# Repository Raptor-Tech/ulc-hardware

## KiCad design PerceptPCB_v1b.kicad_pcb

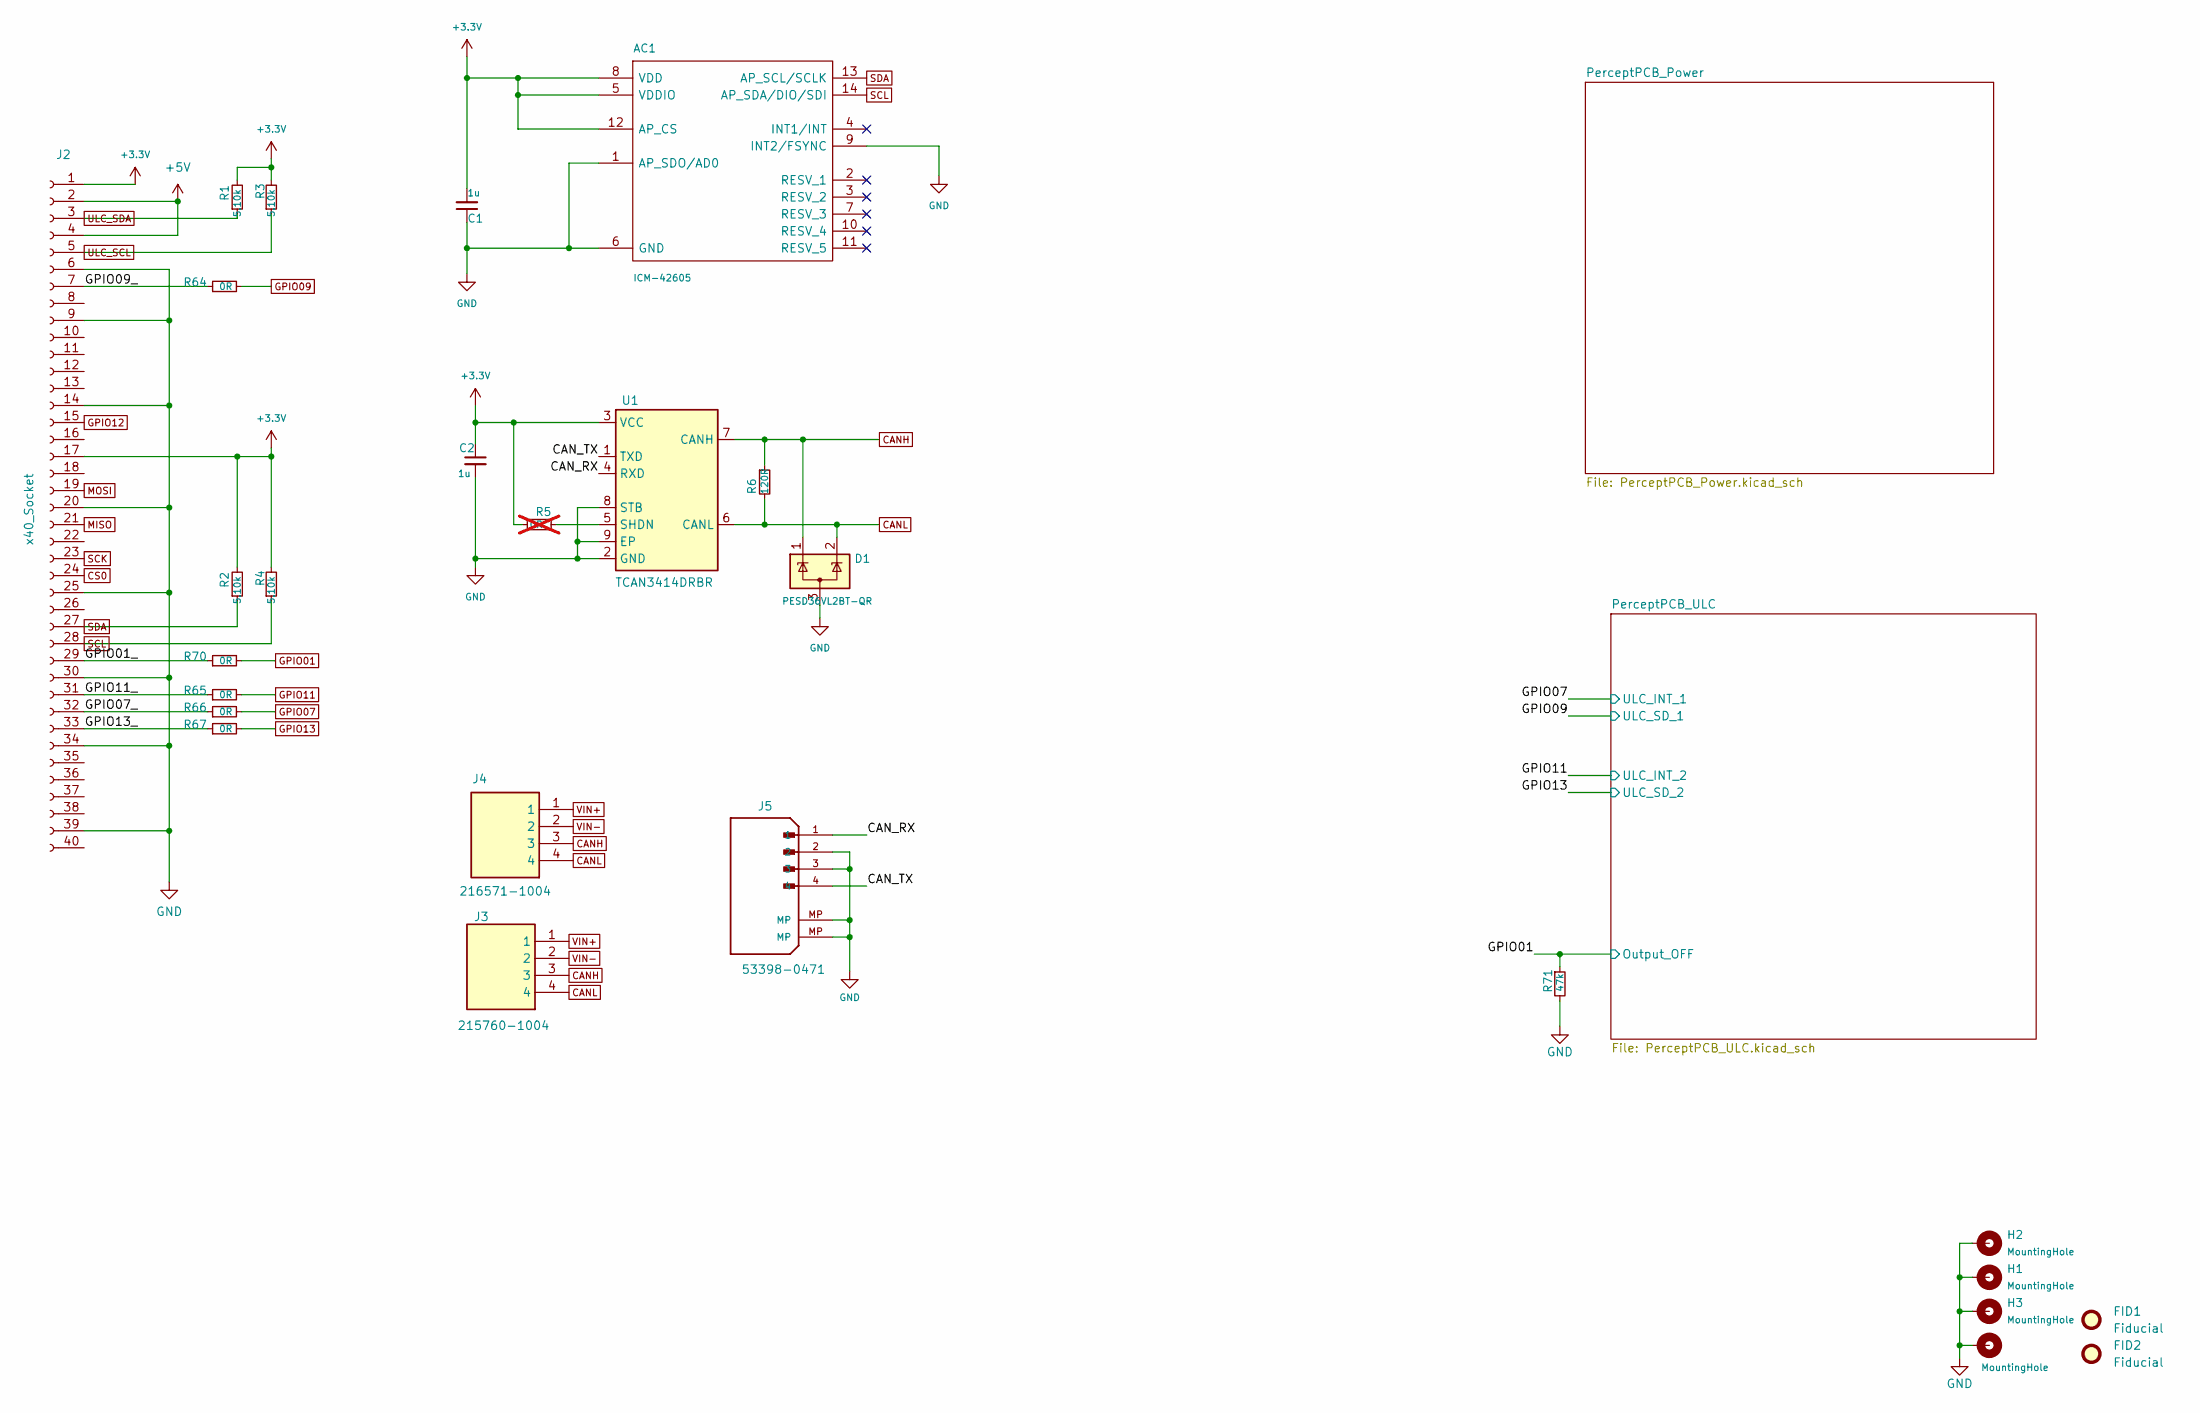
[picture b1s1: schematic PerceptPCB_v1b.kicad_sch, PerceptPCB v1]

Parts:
AC1: ICM-42605; IIM42352; MPN ICM-42605
C1, C2: 1u; C_0603_1608Metric; MPN C1608X7R2A105K080AC
D1: PESD36VL2BT-QR; SOT-23; MPN PESD36VL2BT-QR
FID1, FID2: Fiducial; Fiducial_1mm_Mask2mm
H1, H2, H3: MountingHole; MountingHole_2.7mm_M2.5_ISO14580_Pad
H4: MountingHole; Mounting_Wuerth_WA-SMSI-M1.6_H2.5mm_ThreadDepth1.5mm_NoNPTH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
J2: x40_Socket; PinSocket_2x20_P2.54mm_Vertical_SMD; MPN HLE-120-02-L-DV-BE-A-P-TR
J3: 215760-1004; 215760-YY04; Mouser Part Number 538-215760-1004
J4: 216571-1004; 216571-YY04_1; Mouser Part Number 538-216571-1004
J5: 53398-0471; Molex_PicoBlade_53398-0471_1x04-1MP_P1.25mm_Vertical; MPN 53398-0471
R1, R2, R3, R4: 5.10k; R_0603_1608Metric; MPN RMCF0603FT5K10
R5: 0R; R_0603_1608Metric; MPN RMCF0603ZT0R00; not fitted
R6: 120R; R_0805_2012Metric; MPN CRCW0805120RFKEA
R64, R65, R66, R67, R70: 0R; R_0603_1608Metric; MPN RMCF0603ZT0R00
R71: 47k; R_0603_1608Metric; MPN RMCF0603FT47k0
U1: TCAN3414DRBR; SON65P300X300X100-9N-D; MPN TCAN3414DRBR

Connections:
+3.3V: AC1.5 (VDDIO), AC1.8 (VDD), AC1.12 (AP_CS), C1.2, C2.1, J2.1, J2.17, R1.2, R2.2, R3.2, R4.2, R5.1, U1.3 (VCC); also elsewhere on the board
+5V: J2.2, J2.4
/CAN_RX: J5.1, U1.4 (RXD)
/CAN_TX: J5.4, U1.1 (TXD)
/GPIO01_: J2.29, R70.1
/GPIO07_: J2.32, R66.1
/GPIO09_: J2.7, R64.1
/GPIO11_: J2.31, R65.1
/GPIO13_: J2.33, R67.1
CANH: D1.1 (K), J3.3, J4.3, R6.1, U1.7 (CANH)
CANL: D1.2 (K), J3.4, J4.4, R6.2, U1.6 (CANL)
CS0: J2.24
GND: AC1.1 (AP_SDO/AD0), AC1.6 (GND), AC1.9 (INT2/FSYNC), C1.1, C2.2, D1.3 (A), H1.1, H2.1, H3.1, H4.1, J2.6, J2.9, J2.14, J2.20, J2.25, J2.30, J2.34, J2.39, J5.2, J5.3, J5.MP, R71.2, U1.2 (GND), U1.8 (STB), U1.9 (EP); also elsewhere on the board
GPIO01: R70.2, R71.1; also elsewhere on the board
GPIO07: R66.2; also elsewhere on the board
GPIO09: R64.2; also elsewhere on the board
GPIO11: R65.2; also elsewhere on the board
GPIO12: J2.15
GPIO13: R67.2; also elsewhere on the board
MISO: J2.21
MOSI: J2.19
unnamed: R5.2, U1.5 (SHDN)
SCK: J2.23
SCL: AC1.14 (AP_SDA/DIO/SDI), J2.28, R4.1
SDA: AC1.13 (AP_SCL/SCLK), J2.27, R2.1
ULC_SCL: J2.5, R3.1; also elsewhere on the board
ULC_SDA: J2.3, R1.1; also elsewhere on the board
VIN+: J3.1, J4.1; also elsewhere on the board
VIN-: J3.2, J4.2; also elsewhere on the board

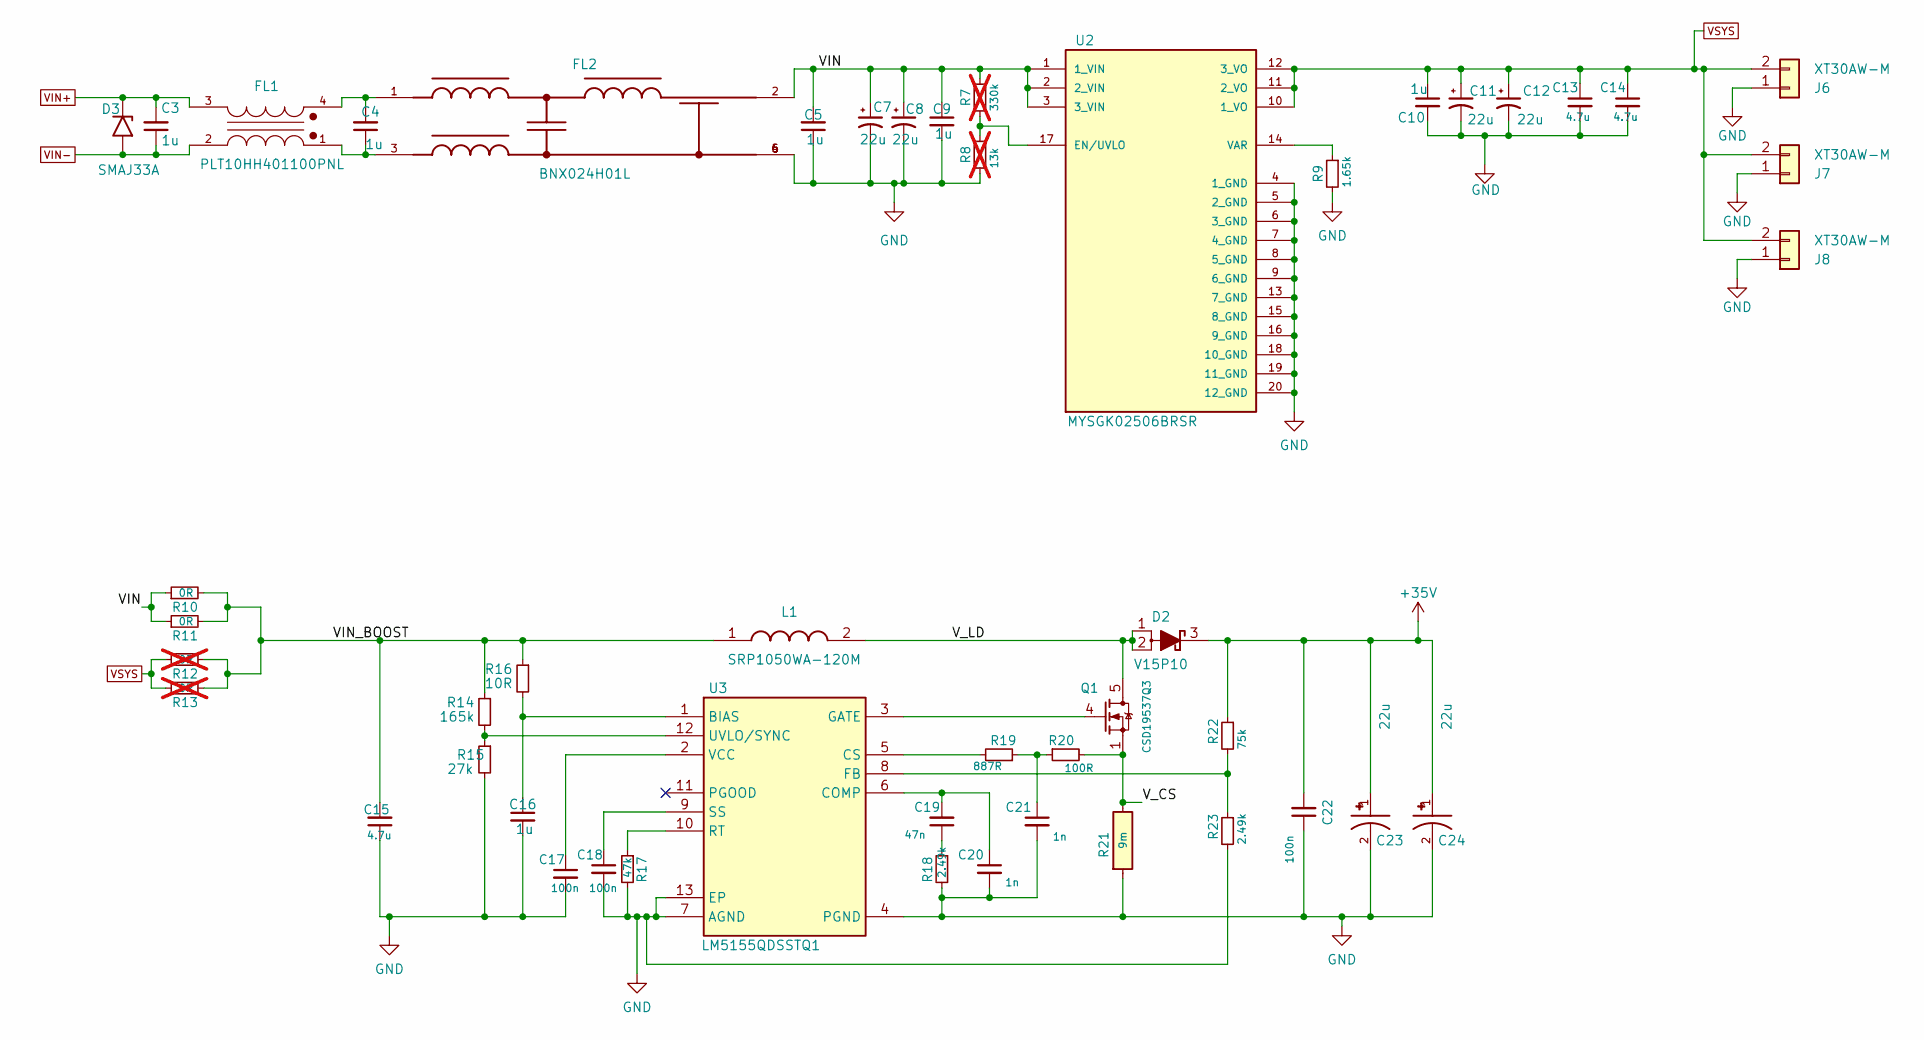
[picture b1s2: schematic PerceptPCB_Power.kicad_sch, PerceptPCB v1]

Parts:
C3, C4, C5: 1u; C_0805_2012Metric; MPN 08051C105K4Z2A
C7, C8, C11, C12, C23, C24: 22u; CAP_EEHZC1J220XV; MPN EEH-ZC1J220XV
C9, C10, C16: 1u; C_0603_1608Metric; MPN C1608X7R2A105K080AC
C13, C14, C15: 4.7u; C_1210_3225Metric_Pad1.33x2.70mm_HandSolder; MPN CL32B475KCVZW6E
C17, C18, C22: 100n; C_0603_1608Metric; MPN CL10B104KC8NNNC
C19: 47n; C_0603_1608Metric; MPN CL10B104KC8NNNC
C20, C21: 1n; C_0603_1608Metric; MPN GCM1885C2A102FA16D
D2: V15P10; TO-277A; MPN V15P10HM3/H
D3: SMAJ33A; D_SMA; MPN SMAJ33A
FL1: PLT10HH401100PNL; FIL_PLT10HH401100PNL
FL2: BNX024H01L; FIL_BNX024H01B; MPN BNX024H01L
J6, J7, J8: XT30AW-M; AMASS_XT30U-M_1x02_P5.0mm_Vertical; MPN XT30AW-M
L1: SRP1050WA-120M; INDPM110100X540N; MPN SRP1050WA-120M
Q1: CSD19537Q3; VSON-8_3.3x3.3mm_P0.65mm_NexFET; MPN CSD19537Q3
R7: 330k; R_0603_1608Metric; MPN CRCW0603330KFKEAC; not fitted
R8: 13k; R_0603_1608Metric; MPN CRCW060313K0FKEAC; not fitted
R9: 1.65k; R_0603_1608Metric; MPN CRCW06031K65FKEA
R10, R11: 0R; R_0603_1608Metric; MPN RMCF0603ZT0R00
R12, R13: 0R; R_0603_1608Metric; MPN RMCF0603ZT0R00; not fitted
R14: 165k; R_0603_1608Metric; MPN CRCW0603165KFKEA
R15: 27k; R_0603_1608Metric; MPN CRCW060327K0FKEA
R16: 10R; R_0603_1608Metric; MPN CRCW060310R0FKEA
R17: 47k; R_0603_1608Metric; MPN RMCF0603FT47k0
R18, R23: 2.49k; R_0603_1608Metric; MPN RMCF0603FT2K49
R19: 887R; R_0603_1608Metric; MPN CRCW0603887RFKEA
R20: 100R; R_0603_1608Metric; MPN RMCF0603FT100R
R21: 9m; R_0612_1632Metric; MPN WFCP06129L000FE66
R22: 75k; R_0603_1608Metric; MPN CRCW060375K0FKEAC
U2: MYSGK02506BRSR; MURATA_MYSGK02506BRSR_0; MOUSER_PART_NUMBER 580-MYSGK02506BRSR
U3: LM5155QDSSTQ1; SON50P200X300X80-13N-D; Mouser Part Number 595-LM5155QDSSTQ1

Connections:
+35V: C22.2, C23.1, C24.1, D2.3 (K), R22.1; also elsewhere on the board
/PerceptPCB_Power/VIN: C5.2, C7.1, C8.1, C9.1, FL2.2, R7.1, R10.1, R11.1, U2.1 (1_VIN), U2.2 (2_VIN), U2.3 (3_VIN)
/PerceptPCB_Power/VIN_BOOST: C15.2, L1.1, R10.2, R11.2, R12.2, R13.2, R14.1, R16.1
/PerceptPCB_Power/V_CS: Q1.1 (S), Q1.2 (S), Q1.3 (S), R20.2, R21.2
/PerceptPCB_Power/V_LD: D2.1 (A), D2.2 (A), L1.2, Q1.5 (D)
GND: C5.1, C7.2, C8.2, C9.2, C10.2, C11.2, C12.2, C13.2, C14.2, C15.1, C16.2, C17.2, C18.2, C20.2, C21.2, C22.1, C23.2, C24.2, FL2.4, FL2.5, FL2.6, J6.1, J7.1, J8.1, R8.2, R9.2, R15.2, R17.2, R18.2, R21.1, R23.2, U2.4 (1_GND), U2.5 (2_GND), U2.6 (3_GND), U2.7 (4_GND), U2.8 (5_GND), U2.9 (6_GND), U2.13 (7_GND), U2.15 (8_GND), U2.16 (9_GND), U2.18 (10_GND), U2.19 (11_GND), U2.20 (12_GND), U3.4 (PGND), U3.7 (AGND), U3.13 (EP); also elsewhere on the board
unnamed: C4.1, FL1.1, FL2.3
unnamed: C4.2, FL1.4, FL2.1
unnamed: C19.1, R18.1
unnamed: C21.1, R19.1, R20.1
unnamed: Q1.4 (G), U3.3 (GATE)
unnamed: R7.2, R8.1, U2.17 (EN/UVLO)
unnamed: R9.1, U2.14 (VAR)
unnamed: C16.1, R16.2, U3.1 (BIAS)
unnamed: C19.2, C20.1, U3.6 (COMP)
unnamed: R19.2, U3.5 (CS)
unnamed: R22.2, R23.1, U3.8 (FB)
unnamed: R17.1, U3.10 (RT)
unnamed: C18.1, U3.9 (SS)
unnamed: R14.2, R15.1, U3.12 (UVLO/SYNC)
unnamed: C17.1, U3.2 (VCC)
VIN+: C3.2, D3.1 (A1), FL1.3; also elsewhere on the board
VIN-: C3.1, D3.2 (A2), FL1.2; also elsewhere on the board
VSYS: C10.1, C11.1, C12.1, C13.1, C14.1, J6.2, J7.2, J8.2, R12.1, R13.1, U2.10 (1_VO), U2.11 (2_VO), U2.12 (3_VO)

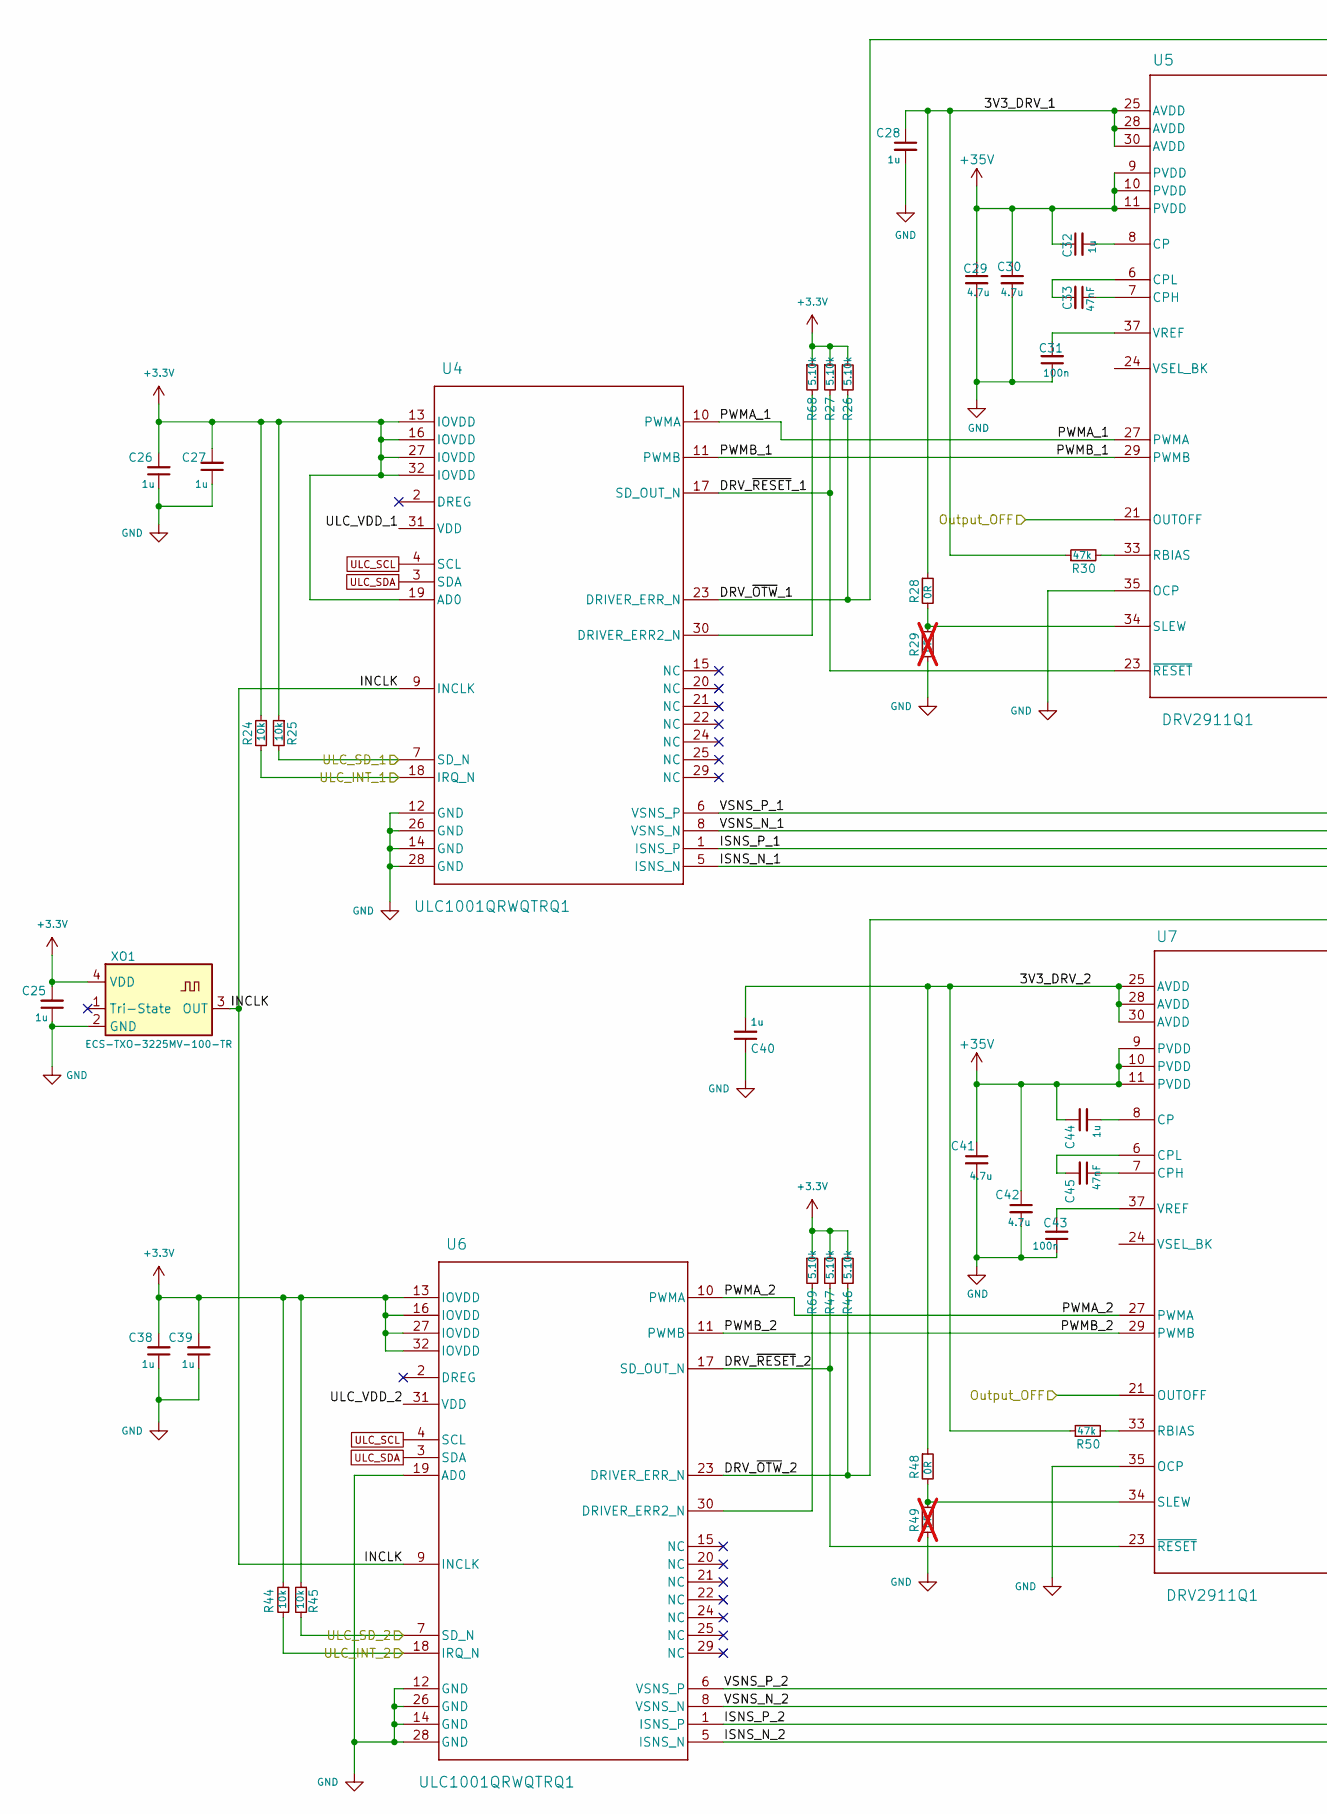
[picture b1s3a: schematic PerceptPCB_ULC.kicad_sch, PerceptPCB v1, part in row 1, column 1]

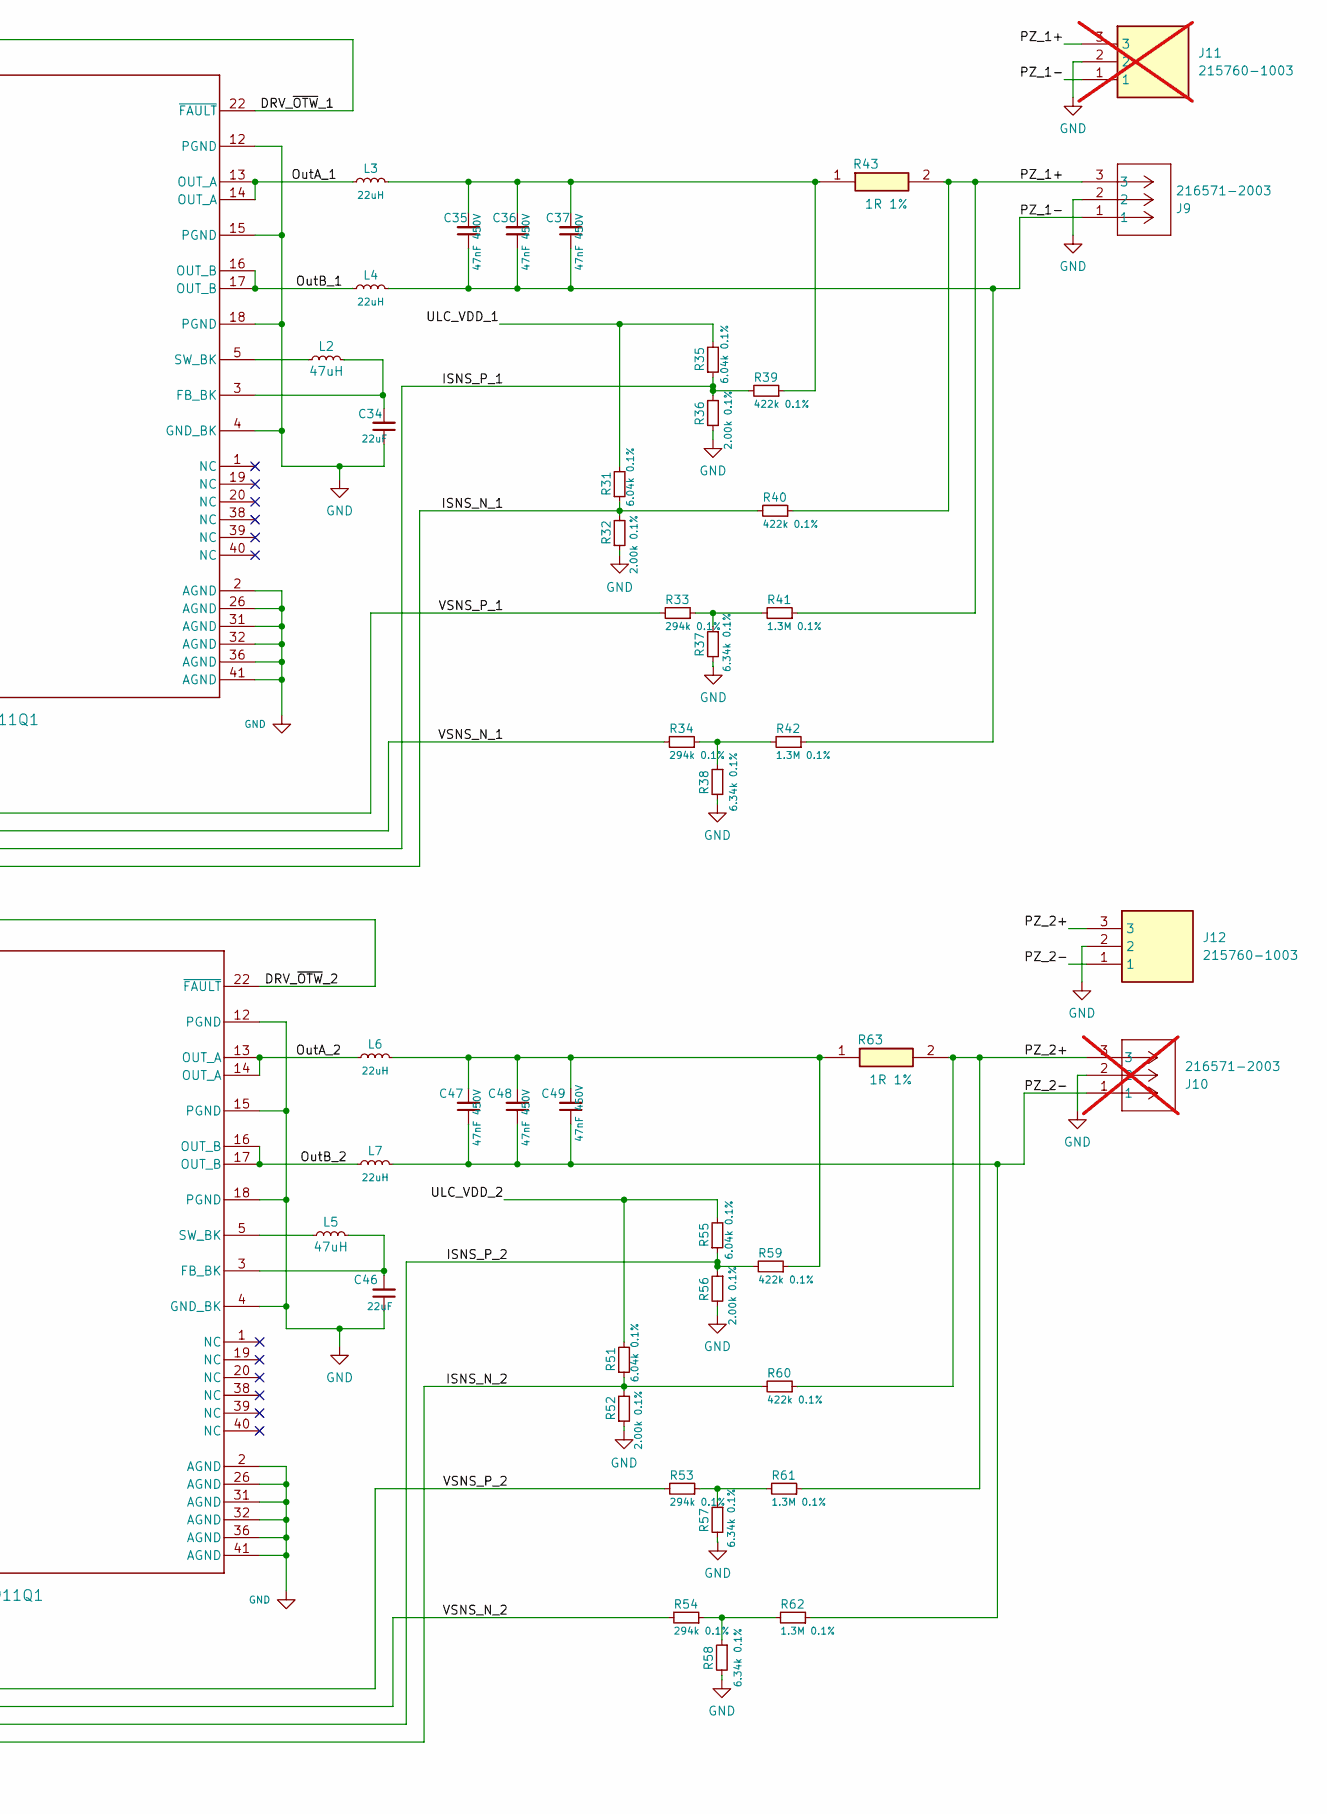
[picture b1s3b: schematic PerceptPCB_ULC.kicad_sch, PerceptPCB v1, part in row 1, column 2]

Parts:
C25, C26, C27, C28, C32, C38, C39, C40, C44: 1u; C_0603_1608Metric; MPN C1608X7R2A105K080AC
C29, C30, C41, C42: 4.7u; C_1210_3225Metric_Pad1.33x2.70mm_HandSolder; MPN CL32B475KCVZW6E
C31, C43: 100n; C_0603_1608Metric; MPN CL10B104KC8NNNC
C33, C45: 47nF; C_0603_1608Metric; MPN C0603C473K5RACTU
C34, C46: 22uF; C_0603_1608Metric; MPN CC0603MRX5R6BB226
C35, C36, C37, C47, C48, C49: 47nF 450V; C_1210_3225Metric_Pad1.33x2.70mm_HandSolder; MPN CGA6M4X7R2J473K200AA
J9: 216571-2003; CONN03_2165712003_MOL; Mouser Part Number 538-215760-1003
J10: 216571-2003; CONN03_2165712003_MOL; Mouser Part Number 538-215760-1003; not fitted
J11: 215760-1003; 215760-YY03; Mouser Part Number 538-215760-1003; not fitted
J12: 215760-1003; 215760-YY03; Mouser Part Number 538-215760-1003
L2, L5: 47uH; L_0805_2012Metric; MPN LQM21DN470M70L
L3, L4, L6, L7: 22uH; 0630CDMCCDS-100MC; PartNumber 0630CDMCCDS-100MC
R24, R25, R44, R45: 10k; R_0603_1608Metric; MPN RMCF0603FT10K0
R26, R27, R46, R47, R68, R69: 5.10k; R_0603_1608Metric; MPN RMCF0603FT5K10
R28, R48: 0R; R_0603_1608Metric; MPN RMCF0603ZT0R00
R29, R49: 0R; R_0603_1608Metric; MPN RMCF0603ZT0R00; not fitted
R30, R50: 47k; R_0603_1608Metric; MPN RMCF0603FT47k0
R31, R35, R51, R55: 6.04k 0.1%; R_0603_1608Metric; MPN TNPW06036K04BEEA
R32, R36, R52, R56: 2.00k 0.1%; R_0603_1608Metric; MPN TNPW06032K00BEEA
R33, R34, R53, R54: 294k 0.1%; R_0603_1608Metric; MPN TNPW0603294KBEEA
R37, R38, R57, R58: 6.34k 0.1%; R_0603_1608Metric; MPN TNPW06036K34BEEA
R39, R40, R59, R60: 422k 0.1%; R_1206_3216Metric; MPN TNPW1206422KBEEA
R41, R42, R61, R62: 1.3M 0.1%; R_1206_3216Metric; MPN RGV3216P-1304-B-T1
R43, R63: 1R 1%; RESC3263X80N; MPN RCL12251R00FKEG
U4, U6: ULC1001QRWQTRQ1; RQT0032A-MFG; MPN ULC1001QRWQTRQ1
U5, U7: DRV2911Q1; QFN50P500X700X100-41N-D; MPN DRV2911Q1
XO1: ECS-TXO-3225MV-100-TR; ECSTXO3225MV100TR; MPN ECS-TXO-3225MV-100-TR

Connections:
+3.3V: C25.2, C26.2, C27.2, C38.2, C39.2, R24.1, R25.1, R26.1, R27.1, R44.1, R45.1, R46.1, R47.1, R68.1, R69.1, U4.13 (IOVDD), U4.16 (IOVDD), U4.19 (AD0), U4.27 (IOVDD), U4.32 (IOVDD), U6.13 (IOVDD), U6.16 (IOVDD), U6.27 (IOVDD), U6.32 (IOVDD), XO1.4 (VDD); also elsewhere on the board
+35V: C29.1, C30.1, C32.1, C41.1, C42.1, C44.1, U5.9 (PVDD), U5.10 (PVDD), U5.11 (PVDD), U7.9 (PVDD), U7.10 (PVDD), U7.11 (PVDD); also elsewhere on the board
/PerceptPCB_ULC/3V3_DRV_1: C28.1, R28.1, R30.1, U5.25 (AVDD), U5.28 (AVDD), U5.30 (AVDD)
/PerceptPCB_ULC/3V3_DRV_2: C40.2, R48.1, R50.1, U7.25 (AVDD), U7.28 (AVDD), U7.30 (AVDD)
/PerceptPCB_ULC/DRV_~OTW_1: R26.2, U4.23 (DRIVER_ERR_N), U5.22 (~FAULT)
/PerceptPCB_ULC/DRV_~OTW_2: R46.2, U6.23 (DRIVER_ERR_N), U7.22 (~FAULT)
/PerceptPCB_ULC/DRV_~RESET_1: R27.2, U4.17 (SD_OUT_N), U5.23 (~RESET)
/PerceptPCB_ULC/DRV_~RESET_2: R47.2, U6.17 (SD_OUT_N), U7.23 (~RESET)
/PerceptPCB_ULC/INCLK: U4.9 (INCLK), U6.9 (INCLK), XO1.3 (OUT)
/PerceptPCB_ULC/ISNS_N_1: R31.1, R32.2, R40.2, U4.5 (ISNS_N)
/PerceptPCB_ULC/ISNS_N_2: R51.1, R52.2, R60.2, U6.5 (ISNS_N)
/PerceptPCB_ULC/ISNS_P_1: R35.1, R36.1, R39.2, U4.1 (ISNS_P)
/PerceptPCB_ULC/ISNS_P_2: R55.1, R56.1, R59.2, U6.1 (ISNS_P)
/PerceptPCB_ULC/OutA_1: L3.1, U5.13 (OUT_A), U5.14 (OUT_A)
/PerceptPCB_ULC/OutA_2: L6.1, U7.13 (OUT_A), U7.14 (OUT_A)
/PerceptPCB_ULC/OutB_1: L4.1, U5.16 (OUT_B), U5.17 (OUT_B)
/PerceptPCB_ULC/OutB_2: L7.1, U7.16 (OUT_B), U7.17 (OUT_B)
/PerceptPCB_ULC/PWMA_1: U4.10 (PWMA), U5.27 (PWMA)
/PerceptPCB_ULC/PWMA_2: U6.10 (PWMA), U7.27 (PWMA)
/PerceptPCB_ULC/PWMB_1: U4.11 (PWMB), U5.29 (PWMB)
/PerceptPCB_ULC/PWMB_2: U6.11 (PWMB), U7.29 (PWMB)
/PerceptPCB_ULC/PZ_1+: J9.3, J11.3, R40.1, R41.1, R43.2
/PerceptPCB_ULC/PZ_1-: C35.1, C36.1, C37.1, J9.1, J11.1, L4.2, R42.1
/PerceptPCB_ULC/PZ_2+: J10.3, J12.3, R60.1, R61.1, R63.2
/PerceptPCB_ULC/PZ_2-: C47.1, C48.1, C49.1, J10.1, J12.1, L7.2, R62.1
/PerceptPCB_ULC/ULC_VDD_1: R31.2, R35.2, U4.31 (VDD)
/PerceptPCB_ULC/ULC_VDD_2: R51.2, R55.2, U6.31 (VDD)
/PerceptPCB_ULC/VSNS_N_1: R34.2, U4.8 (VSNS_N)
/PerceptPCB_ULC/VSNS_N_2: R54.2, U6.8 (VSNS_N)
/PerceptPCB_ULC/VSNS_P_1: R33.2, U4.6 (VSNS_P)
/PerceptPCB_ULC/VSNS_P_2: R53.2, U6.6 (VSNS_P)
GND: C25.1, C26.1, C27.1, C28.2, C29.2, C30.2, C31.1, C34.1, C38.1, C39.1, C40.1, C41.2, C42.2, C43.1, C46.1, J9.2, J10.2, J11.2, J12.2, R29.2, R32.1, R36.2, R37.2, R38.2, R49.2, R52.1, R56.2, R57.2, R58.2, U4.12 (GND), U4.14 (GND), U4.26 (GND), U4.28 (GND), U5.2 (AGND), U5.4 (GND_BK), U5.12 (PGND), U5.15 (PGND), U5.18 (PGND), U5.26 (AGND), U5.31 (AGND), U5.32 (AGND), U5.35 (OCP), U5.36 (AGND), U5.41 (AGND), U6.12 (GND), U6.14 (GND), U6.19 (AD0), U6.26 (GND), U6.28 (GND), U7.2 (AGND), U7.4 (GND_BK), U7.12 (PGND), U7.15 (PGND), U7.18 (PGND), U7.26 (AGND), U7.31 (AGND), U7.32 (AGND), U7.35 (OCP), U7.36 (AGND), U7.41 (AGND), XO1.2 (GND); also elsewhere on the board
GPIO01: U5.21 (OUTOFF), U7.21 (OUTOFF); also elsewhere on the board
GPIO07: R24.2, U4.18 (IRQ_N); also elsewhere on the board
GPIO09: R25.2, U4.7 (SD_N); also elsewhere on the board
GPIO11: R44.2, U6.18 (IRQ_N); also elsewhere on the board
GPIO13: R45.2, U6.7 (SD_N); also elsewhere on the board
unnamed: C35.2, C36.2, C37.2, L3.2, R39.1, R43.1
unnamed: C47.2, C48.2, C49.2, L6.2, R59.1, R63.1
unnamed: R33.1, R37.1, R41.2
unnamed: R34.1, R38.1, R42.2
unnamed: R53.1, R57.1, R61.2
unnamed: R54.1, R58.1, R62.2
unnamed: R68.2, U4.30 (DRIVER_ERR2_N)
unnamed: C32.2, U5.8 (CP)
unnamed: C33.1, U5.7 (CPH)
unnamed: C33.2, U5.6 (CPL)
unnamed: C34.2, L2.2, U5.3 (FB_BK)
unnamed: R30.2, U5.33 (RBIAS)
unnamed: R28.2, R29.1, U5.34 (SLEW)
unnamed: L2.1, U5.5 (SW_BK)
unnamed: C31.2, U5.37 (VREF)
unnamed: R69.2, U6.30 (DRIVER_ERR2_N)
unnamed: C44.2, U7.8 (CP)
unnamed: C45.1, U7.7 (CPH)
unnamed: C45.2, U7.6 (CPL)
unnamed: C46.2, L5.2, U7.3 (FB_BK)
unnamed: R50.2, U7.33 (RBIAS)
unnamed: R48.2, R49.1, U7.34 (SLEW)
unnamed: L5.1, U7.5 (SW_BK)
unnamed: C43.2, U7.37 (VREF)
ULC_SCL: U4.4 (SCL), U6.4 (SCL); also elsewhere on the board
ULC_SDA: U4.3 (SDA), U6.3 (SDA); also elsewhere on the board

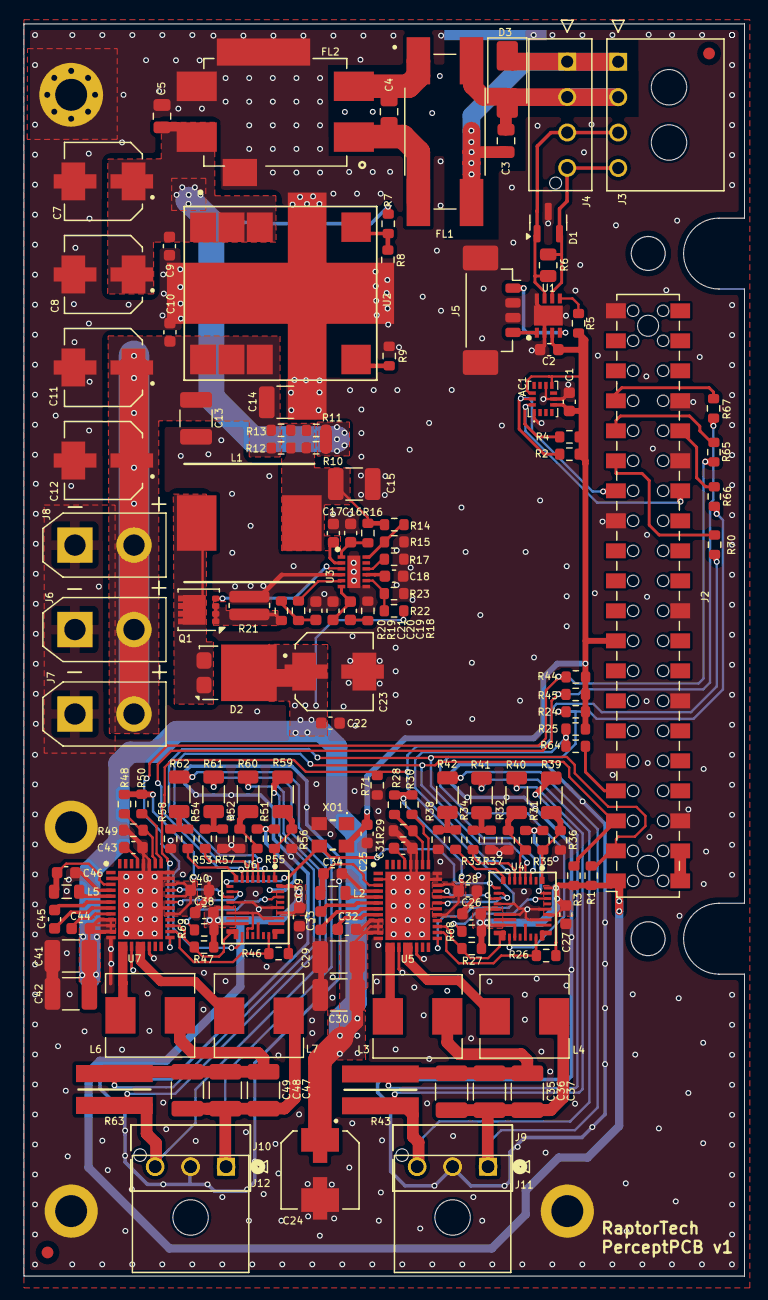
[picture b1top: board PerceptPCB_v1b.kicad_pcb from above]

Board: 4 copper layers, 61.0 x 106.0 mm, 158 parts (0 on the bottom side), 98 nets.
